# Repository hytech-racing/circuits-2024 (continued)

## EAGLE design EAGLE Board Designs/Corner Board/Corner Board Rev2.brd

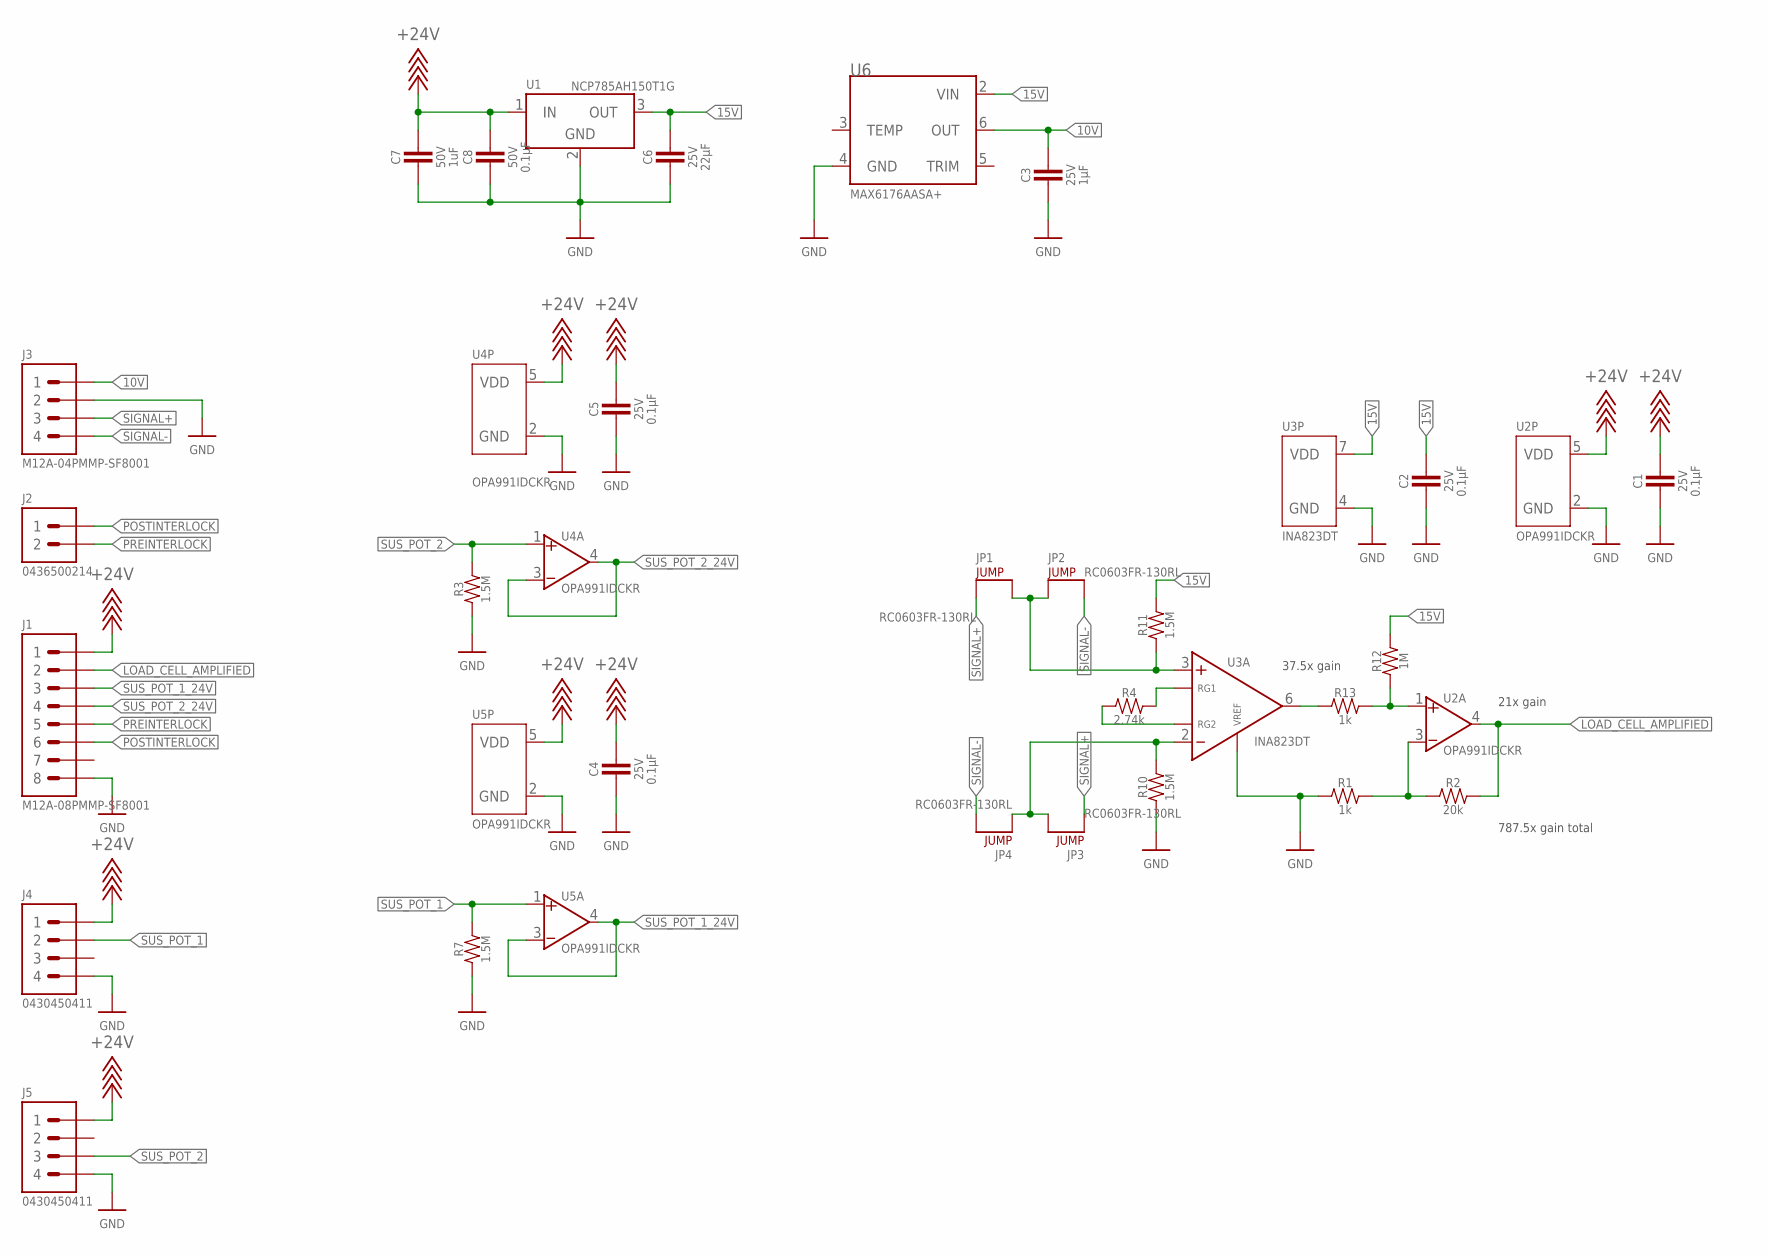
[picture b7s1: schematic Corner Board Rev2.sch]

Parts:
C1, C2, C4, C5: CAPACITOR_0603_25V_0.1UF; 0603-CAP
C3: CAPACITOR_0603_25V_1UF; 0603-CAP
C6: CAPACITOR_0805_25V_22UF; 0805-CAP
C7: CAPACITOR_0603_50V_1UF; 0603-CAP
C8: CAPACITOR_0603_50V_0.1UF; 0603-CAP
J1: CONNECTOR-8_AMPHENOL_M12A_08PMMP_; M12A-08PMMP
J2: CONNECTOR-2_MICROFIT_SMD_RIGHTANGLE_02_SINGLE_BLA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; MOLEX_MICROFIT_SMD_RIGHTANGLE_02_SINGLE
J3: CONNECTOR-4_AMPHENOL_M12A_04PMMP_; M12A-04PMMP
J4, J5: CONNECTOR-4_μF_S_RA_; MOLEX_MICROFIT_SMD_RIGHTANGLE_04_DUAL
JP1, JP2, JP3, JP4: JUMPER_0603_; 0603-RES
R1, R13: RESISTOR_0603_1K; 0603-RES
R2: RESISTOR_0603_20K; 0603-RES
R3, R7, R10, R11: RESISTOR_0603_1.5M; 0603-RES
R4: RESISTOR_0603_2.74K; 0603-RES
R12: RESISTOR_0603_1M; 0603-RES
U1: VOLTAGE_REGULATOR_SOT-89_15V; SOT-89
U2, U4, U5: OPAMP_1_CHANNEL_OPA991; SC-70-5
U3: INA823DT; SOIC-08(NARROW,0.15")
U6: VOLTAGE_REFERENCE_SOIC-8_10V; SOIC-08(NARROW,0.15")

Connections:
10V: C3.1, J3.1, U6.6 (OUT)
15V: C2.1, C6.1, R11.2, R12.2, U1.3 (OUT), U3.7 (VDD), U6.2 (VIN)
+24V: C1.1, C4.1, C5.1, C7.1, C8.1, J1.1, J4.1, J5.1, U1.1 (IN), U2.5 (VDD), U4.5 (VDD), U5.5 (VDD)
GND: C1.2, C2.2, C3.2, C4.2, C5.2, C6.2, C7.2, C8.2, J1.8, J3.2, J4.4, J5.4, R1.1, R3.1, R7.1, R10.1, U1.2 (GND), U2.2 (GND), U3.4 (GND), U3.5 (VREF), U4.2 (GND), U5.2 (GND), U6.4 (GND)
LOAD_CELL_AMPLIFIED: J1.2, R2.2, U2.4 (VOUT)
unnamed: R1.2, R2.1, U2.3 (VIN-)
unnamed: R4.2, U3.1 (RG1)
unnamed: R13.1, U3.6 (VOUT)
unnamed: R4.1, U3.8 (RG2)
unnamed: R12.1, R13.2, U2.1 (VIN+)
unnamed: JP3.2, JP4.1, R10.2, U3.2 (VIN-)
unnamed: JP1.2, JP2.1, R11.1, U3.3 (VIN+)
POSTINTERLOCK: J1.6, J2.1
PREINTERLOCK: J1.5, J2.2
SIGNAL+: J3.3, JP1.1, JP3.1
SIGNAL-: J3.4, JP2.2, JP4.2
SUS_POT_1: J4.2, R7.2, U5.1 (VIN+)
SUS_POT_1_24V: J1.3, U5.3 (VIN-), U5.4 (VOUT)
SUS_POT_2: J5.3, R3.2, U4.1 (VIN+)
SUS_POT_2_24V: J1.4, U4.3 (VIN-), U4.4 (VOUT)

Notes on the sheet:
37.5x gain
21x gain
787.5x gain total

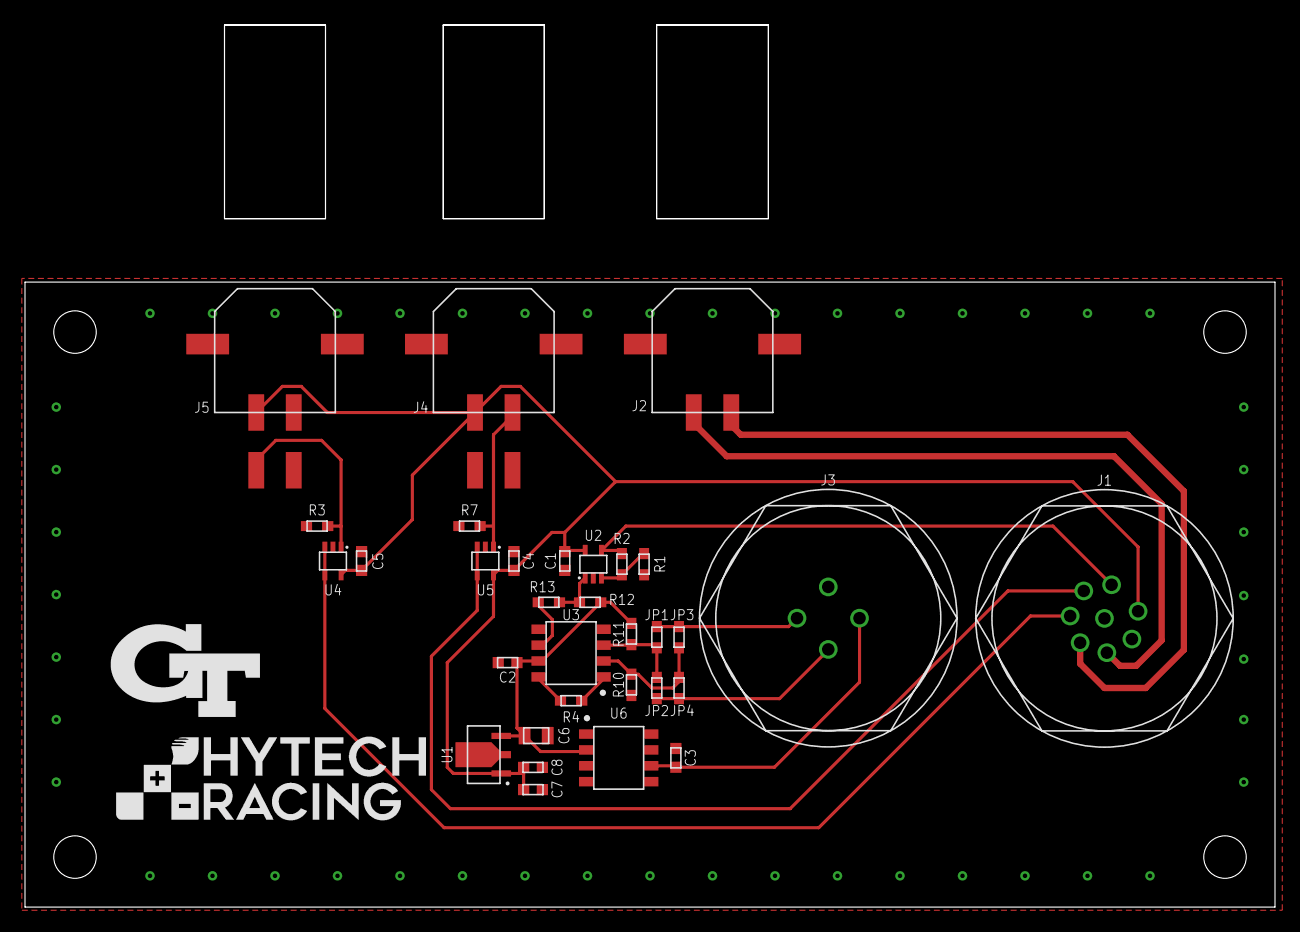
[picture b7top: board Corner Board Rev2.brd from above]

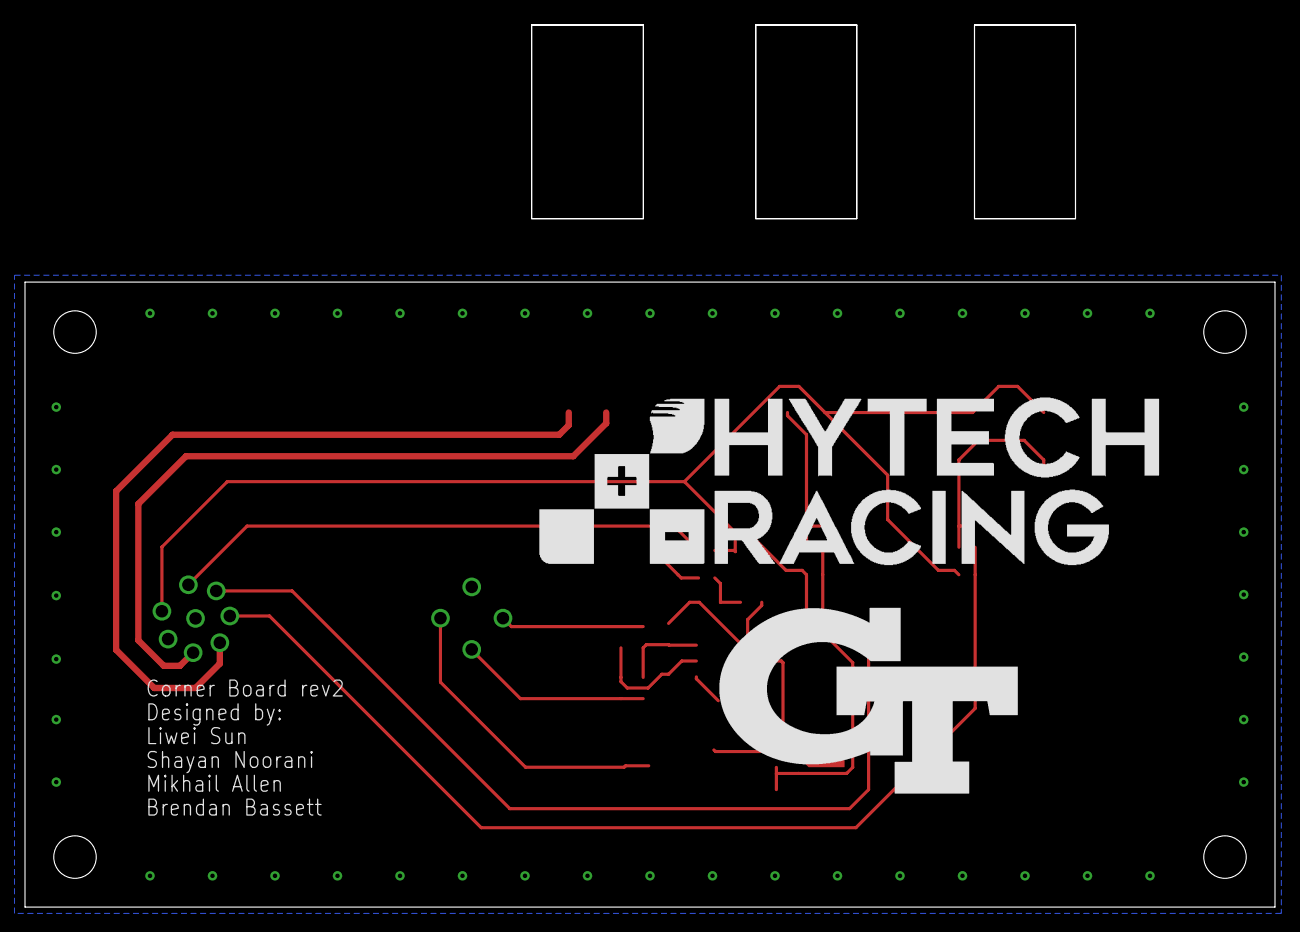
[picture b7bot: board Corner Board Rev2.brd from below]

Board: 2 copper layers, 100.0 x 50.0 mm, 40 parts (2 on the bottom side), 20 nets.

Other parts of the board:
U$6: LOGO_HYTECH_LARGE
U$7, U$8, U$9, U$10: MOUNTING_M3
U$13: LOGO_HYTECH_MEDIUM
U$14: LOGO_GT_MEDIUM
U$15: LOGO_GT_LARGE
